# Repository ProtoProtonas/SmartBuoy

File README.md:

# SmartBuoy
Repository for a smart buoy which can navigate to a destination on water and then come back.

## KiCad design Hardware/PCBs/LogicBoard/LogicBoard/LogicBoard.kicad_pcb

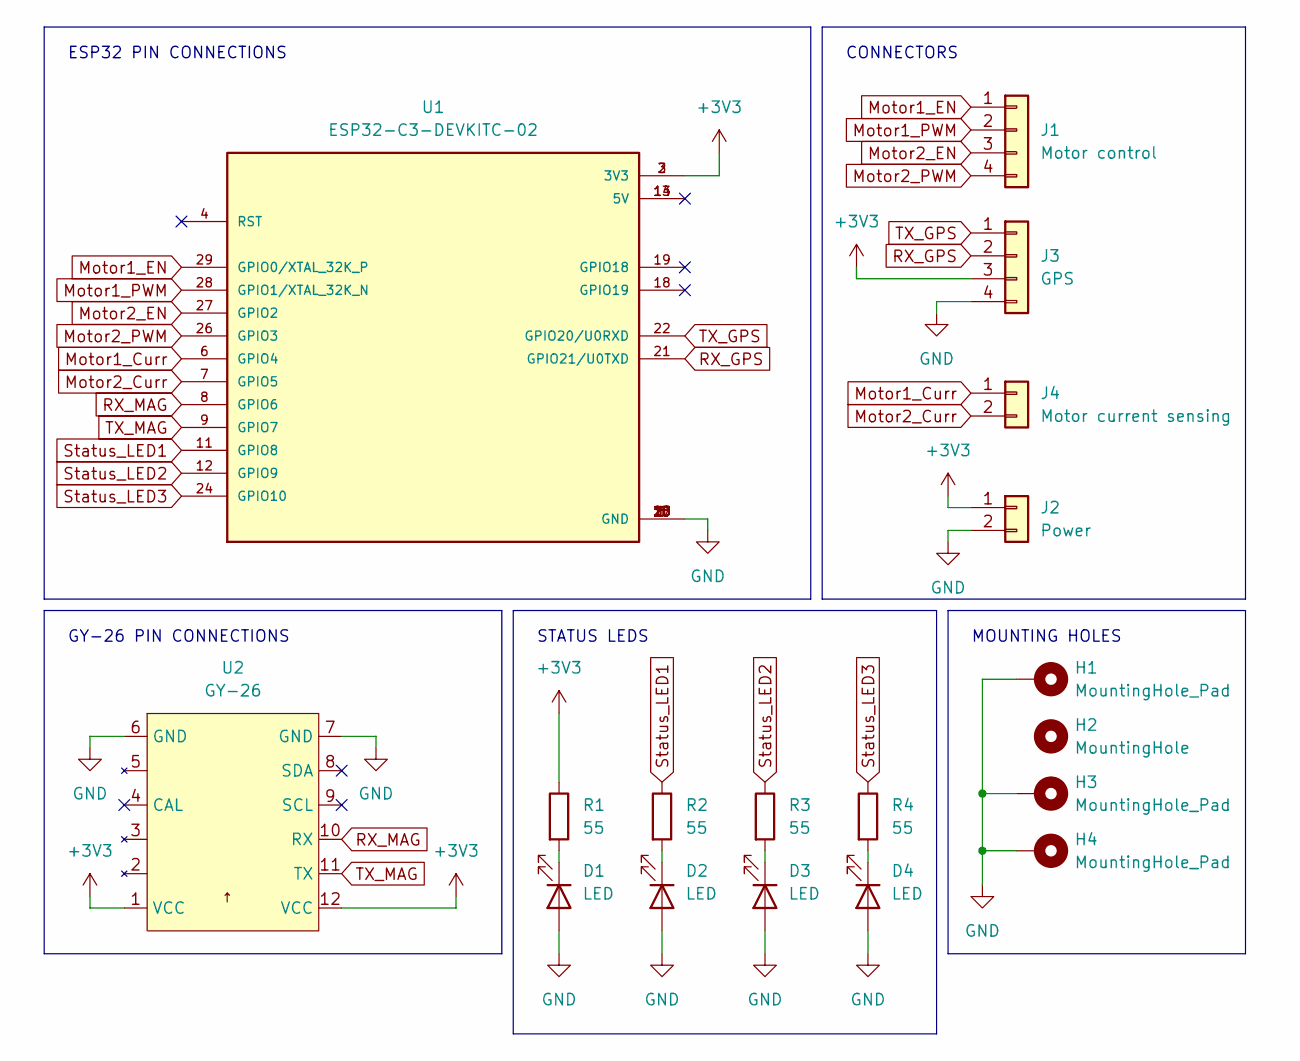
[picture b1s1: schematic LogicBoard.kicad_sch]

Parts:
D1, D2, D3, D4: LED; LED_0603_1608Metric_Pad1.05x0.95mm_HandSolder
H1: MountingHole_Pad; MountingHole_2.2mm_M2_DIN965_Pad_TopBottom
H2: MountingHole; MountingHole_2.2mm_M2_DIN965
H3, H4: MountingHole_Pad; MountingHole_2.2mm_M2_ISO7380_Pad_TopBottom
J1: Motor control; PinHeader_1x04_P2.54mm_Vertical
J2: Power; PinHeader_1x02_P2.54mm_Vertical
J3: GPS; PinHeader_1x04_P2.54mm_Vertical
J4: Motor current sensing; PinHeader_1x02_P2.54mm_Vertical
R1, R2, R3, R4: 55; R_0603_1608Metric_Pad0.98x0.95mm_HandSolder
U1: ESP32-C3-DEVKITC-02; XCVR_ESP32-C3-DEVKITC-02
U2: GY-26

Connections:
+3V3: J2.1, J3.3, R1.1, U1.2 (3V3), U1.3 (3V3), U2.1 (VCC), U2.12 (VCC)
GND: D1.2 (A), D2.2 (A), D3.2 (A), D4.2 (A), H1.1, H3.1, H4.1, J2.2, J3.4, U1.1 (GND), U1.5 (GND), U1.10 (GND), U1.15 (GND), U1.16 (GND), U1.17 (GND), U1.20 (GND), U1.23 (GND), U1.25 (GND), U1.30 (GND), U2.6 (GND), U2.7 (GND)
Motor1_Curr: J4.1, U1.6 (GPIO4)
Motor1_EN: J1.1, U1.29 (GPIO0/XTAL_32K_P)
Motor1_PWM: J1.2, U1.28 (GPIO1/XTAL_32K_N)
Motor2_Curr: J4.2, U1.7 (GPIO5)
Motor2_EN: J1.3, U1.27 (GPIO2)
Motor2_PWM: J1.4, U1.26 (GPIO3)
unnamed: D1.1 (K), R1.2
unnamed: D2.1 (K), R2.2
unnamed: D3.1 (K), R3.2
unnamed: D4.1 (K), R4.2
RX_GPS: J3.2, U1.21 (GPIO21/U0TXD)
RX_MAG: U1.8 (GPIO6), U2.10 (RX)
Status_LED1: R2.1, U1.11 (GPIO8)
Status_LED2: R3.1, U1.12 (GPIO9)
Status_LED3: R4.1, U1.24 (GPIO10)
TX_GPS: J3.1, U1.22 (GPIO20/U0RXD)
TX_MAG: U1.9 (GPIO7), U2.11 (TX)

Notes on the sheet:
MOUNTING HOLES
CONNECTORS
GY-26 PIN CONNECTIONS
STATUS LEDS
ESP32 PIN CONNECTIONS

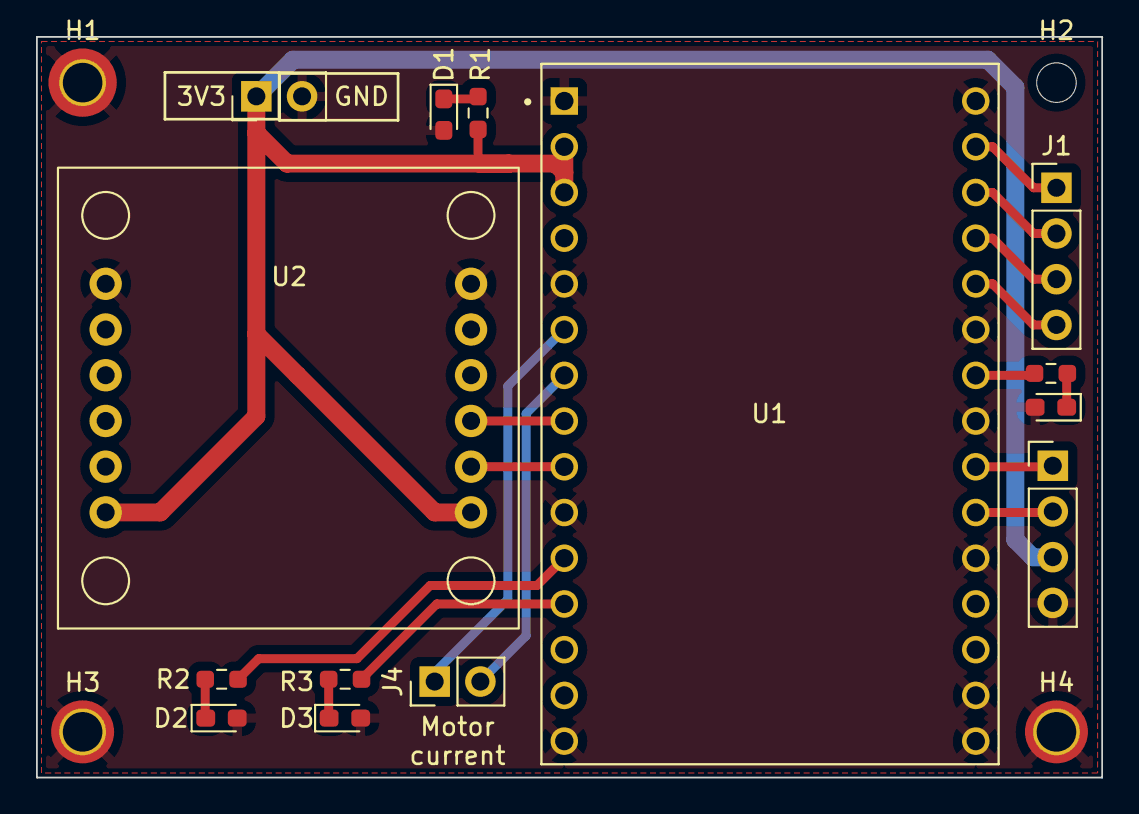
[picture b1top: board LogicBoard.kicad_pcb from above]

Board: 2 copper layers, 59.2 x 41.1 mm, 18 parts (0 on the bottom side), 19 nets.

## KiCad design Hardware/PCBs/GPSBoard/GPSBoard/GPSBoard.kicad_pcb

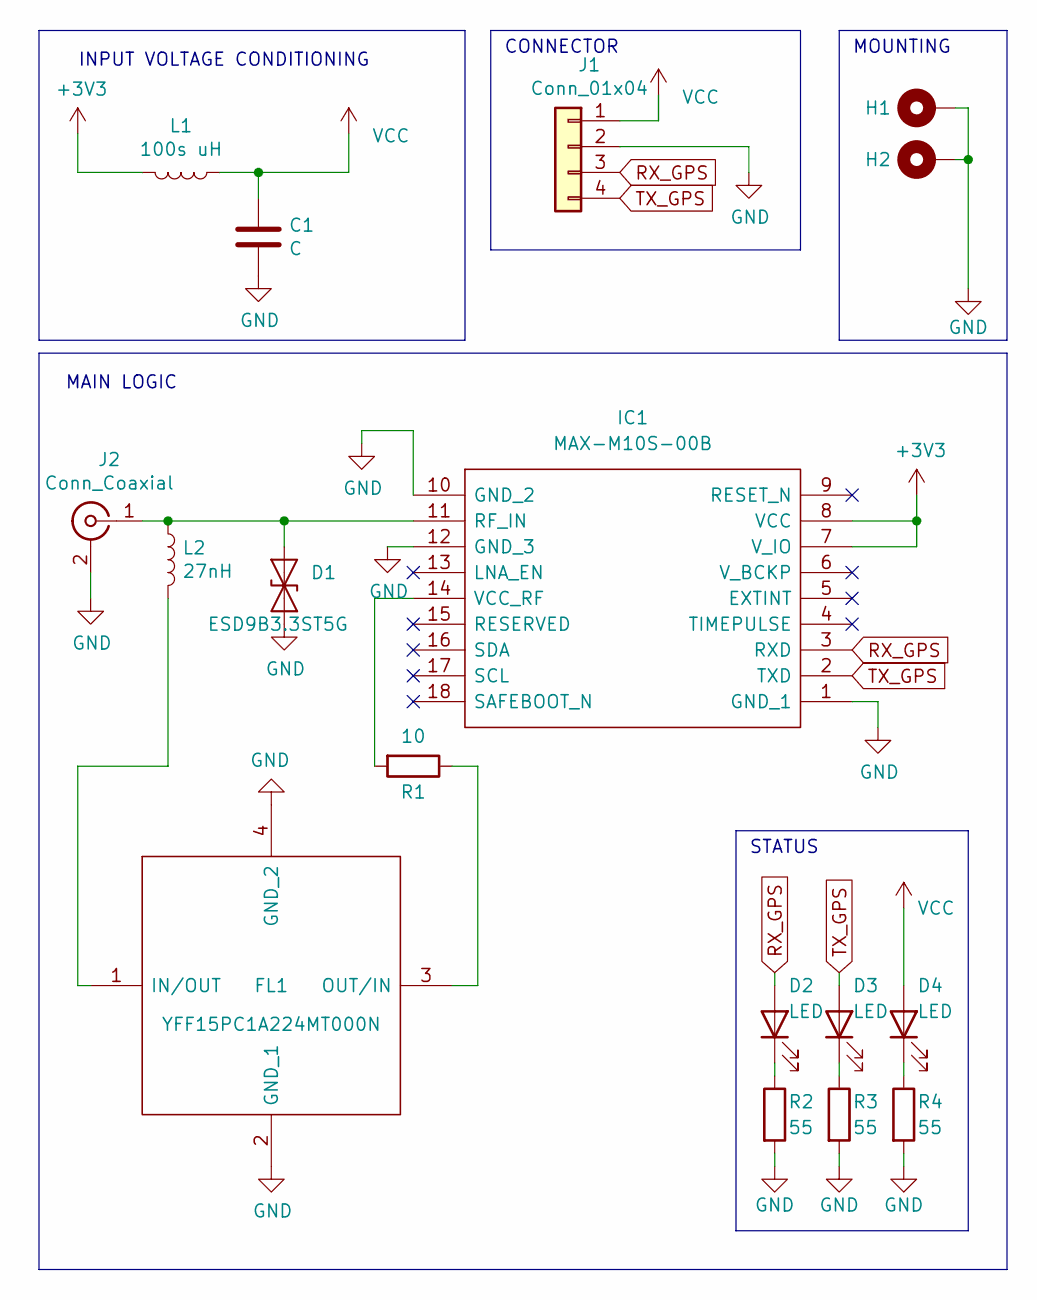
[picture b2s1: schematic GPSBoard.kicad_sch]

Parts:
C1: C; C_1206_3216Metric_Pad1.33x1.80mm_HandSolder
D1: ESD9B3.3ST5G; D_SOD-923
D2, D3, D4: LED; LED_0603_1608Metric_Pad1.05x0.95mm_HandSolder
FL1: YFF15PC1A224MT000N; YFF15PC; Mouser Part Number 810-YFF15PC1A224M
H1, H2: MountingHole_Pad; MountingHole_2.2mm_M2_Pad_TopBottom
IC1: MAX-M10S-00B; MAXM10S00B; Mouser Part Number 377-MAX-M10S-00B
J1: Conn_01x04; PinHeader_1x04_P2.54mm_Vertical
J2: Conn_Coaxial; U.FL_Molex_MCRF_73412-0110_Vertical
L1: 100s uH; L_1206_3216Metric_Pad1.22x1.90mm_HandSolder
L2: 27nH; L_1206_3216Metric_Pad1.22x1.90mm_HandSolder
R1: 10; R_1206_3216Metric_Pad1.30x1.75mm_HandSolder
R2, R3, R4: 55; R_0603_1608Metric_Pad0.98x0.95mm_HandSolder

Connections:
+3V3: IC1.7 (V_IO), IC1.8 (VCC), L1.2
GND: C1.2, D1.1 (A1), FL1.2 (GND_1), FL1.4 (GND_2), H1.1, H2.1, IC1.1 (GND_1), IC1.10 (GND_2), IC1.12 (GND_3), J1.2, J2.2 (Ext), R2.2, R3.2, R4.2
unnamed: D1.2 (A2), IC1.11 (RF_IN), J2.1 (In), L2.1
unnamed: D2.1 (K), R2.1
unnamed: D3.1 (K), R3.1
unnamed: D4.1 (K), R4.1
unnamed: FL1.1 (IN/OUT), L2.2
unnamed: FL1.3 (OUT/IN), R1.1
unnamed: IC1.14 (VCC_RF), R1.2
RX_GPS: D2.2 (A), IC1.3 (RXD), J1.3
TX_GPS: D3.2 (A), IC1.2 (TXD), J1.4
VCC: C1.1, D4.2 (A), J1.1, L1.1

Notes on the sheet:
CONNECTOR
STATUS
MOUNTING
INPUT VOLTAGE CONDITIONING
MAIN LOGIC

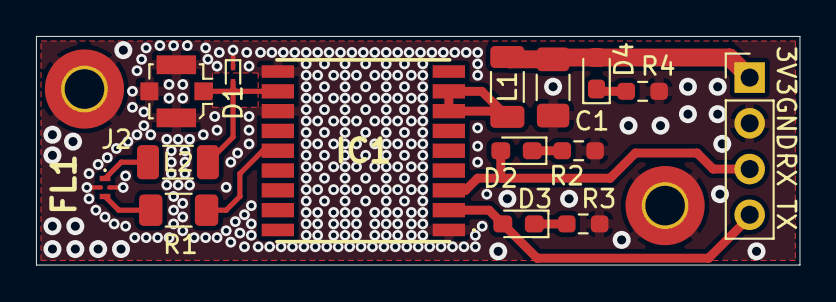
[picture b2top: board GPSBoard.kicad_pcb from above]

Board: 2 copper layers, 42.4 x 12.7 mm, 17 parts (0 on the bottom side), 12 nets.

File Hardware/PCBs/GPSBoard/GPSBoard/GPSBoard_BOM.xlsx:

Source: | C:\Users\Augustas\Desktop\shrot\projektukai\ESP32buoy\git\SmartBuoy\Hardware\PC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
Date: | 44914.83315972222
Tool: | Eeschema (6.0.9)
Generator: | C:\Program Files\KiCad\6.0\bin\scripting\plugins/bom_csv_grouped_by_value_with_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
Component Count: | 19
Ref | Qnty | Value | Cmp name | Footprint | Description | Vendor
C1 , | 1 | 10u | C | Capacitor_SMD:C_1206_3216Metric_Pad1.33x1.80mm_HandSolder | Unpolarized capacitor | https://eu.mouser.com/ProductDetail/KYOCERA-AVX/1206DD106MAT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
C2 , | 1 | <12pF | C_Feedthrough | YFF18AC0G475MT0Y0E:YFF18AC | Feedthrough capacitor | https://eu.mouser.com/ProductDetail/TDK/YFF18AC0G475MT0Y0E?q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
D1 , | 1 | ESD9B3.3ST5G | ESD9B3.3ST5G | Diode_SMD:D_SOD-923 | ESD protection diode, 3.3Vrwm, SOD-923 | https://eu.mouser.com/ProductDetail/onsemi/ESD9B3.3ST5G?qs=y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
D2 ,D3 ,D4 , | 3 | LED | LED | LED_SMD:LED_0603_1608Metric_Pad1.05x0.95mm_HandSolder | Light emitting diode | https://eu.mouser.com/ProductDetail/ROHM-Semiconductor/SML-D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 | https://eu.mouser.com/ProductDetail/Bivar/SM0603UBWC?qs=hWDd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 | https://eu.mouser.com/ProductDetail/Lumex/SML-LX0603GW-TR?qs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 | https://eu.mouser.com/ProductDetail/Lumex/SML-LXIL0603SYC-TR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
H1 ,H2 ,H3 ,H4 , | 4 | MountingHole_Pad | MountingHole_Pad | MountingHole:MountingHole_2.2mm_M2_Pad_TopBottom | Mounting Hole with connection
IC1 , | 1 | MAX-M10S-00B | MAX-M10S-00B | UBLOX_GPS:MAXM10S00B | GPS Modules u-blox M10 GNSS LCC module, firmware in ROM, SAW filter, LNA | https://eu.mouser.com/ProductDetail/u-blox/MAX-M10S-00B?qs=A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
J1 , | 1 | Conn_01x04 | Conn_01x04 | Connector_PinHeader_2.54mm:PinHeader_1x04_P2.54mm_Vertical | Generic connector, single row, 01x04, script generated (kicad-library-utils/sch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 | https://eu.mouser.com/ProductDetail/Wurth-Elektronik/6130401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
J2 , | 1 | Conn_Coaxial | Conn_Coaxial | Connector_Coaxial:U.FL_Hirose_U.FL-R-SMT-1_Vertical | coaxial connector (BNC, SMA, SMB, SMC, Cinch/RCA, LEMO, ...) | https://eu.mouser.com/ProductDetail/Linx-Technologies/CONUFL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
L1 , | 1 | 100s uH | L | Inductor_SMD:L_1206_3216Metric_Pad1.22x1.90mm_HandSolder | Inductor | https://eu.mouser.com/ProductDetail/Murata-Electronics/LQM31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
L2 , | 1 | 27nH | L | Inductor_SMD:L_1206_3216Metric_Pad1.22x1.90mm_HandSolder | Inductor | https://eu.mouser.com/ProductDetail/Coilcraft/1206CS-270XGLC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 | https://eu.mouser.com/ProductDetail/Murata-Electronics/LQW31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
R1 , | 1 | 10 | R | Resistor_SMD:R_1206_3216Metric_Pad1.30x1.75mm_HandSolder | Resistor | https://eu.mouser.com/ProductDetail/Bourns/CRT1206-BY-10R0EL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
R2 ,R3 ,R4 , | 3 | 55 | R | Resistor_SMD:R_0603_1608Metric_Pad0.98x0.95mm_HandSolder | Resistor | https://eu.mouser.com/ProductDetail/Vishay-Dale/CRCW060356R0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
 |  |  |  |  |  | https://eu.mouser.com/ProductDetail/Linx-Technologies/ANT-GN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

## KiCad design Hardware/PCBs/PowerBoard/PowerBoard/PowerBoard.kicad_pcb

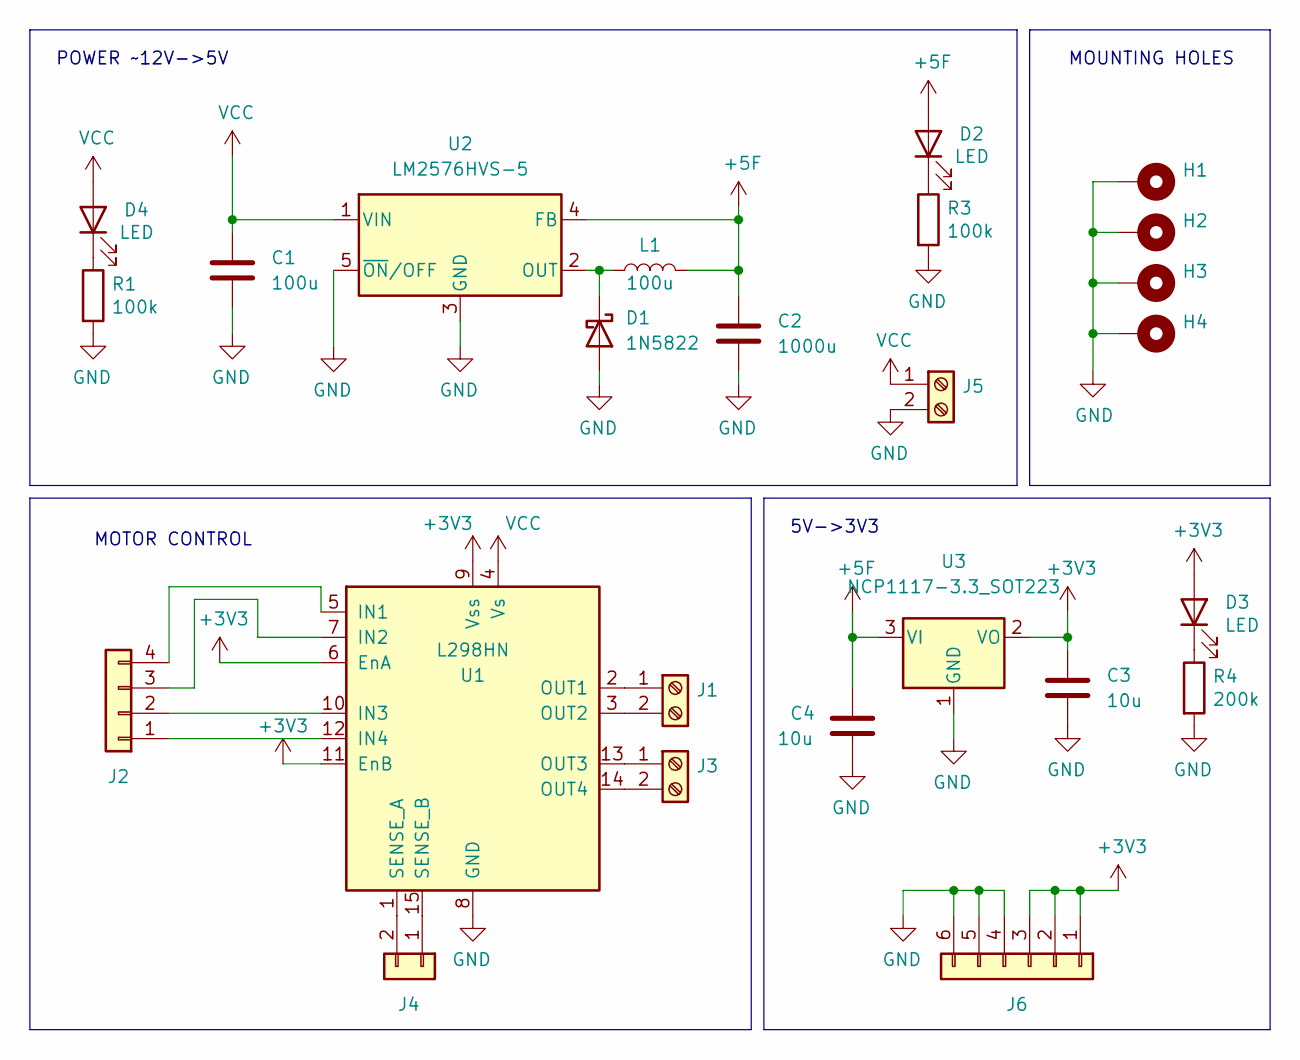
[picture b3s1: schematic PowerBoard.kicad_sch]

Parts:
C1: 100u; CP_Radial_D8.0mm_P3.50mm
C2: 1000u; CP_Radial_D16.0mm_P7.50mm
C3, C4: 10u; C_1206_3216Metric_Pad1.33x1.80mm_HandSolder
D1: 1N5822; D_DO-201AD_P15.24mm_Horizontal
D2, D3, D4: LED; LED_D5.0mm
H1, H2, H3, H4: MountingHole_Pad; MountingHole_3.2mm_M3_DIN965_Pad_TopBottom
J1, J3, J5: Screw_Terminal_01x02; TerminalBlock_bornier-2_P5.08mm
J2: Conn_01x04; PinSocket_1x04_P2.54mm_Vertical
J4: Conn_01x02; PinSocket_1x02_P2.54mm_Vertical
J6: Conn_01x06; PinSocket_1x06_P2.54mm_Vertical
L1: 100u; L_1812_4532Metric_Pad1.30x3.40mm_HandSolder
R1: 100k; R_0603_1608Metric_Pad0.98x0.95mm_HandSolder
R3: 100k; R_0805_2012Metric_Pad1.20x1.40mm_HandSolder
R4: 200k; R_0603_1608Metric_Pad0.98x0.95mm_HandSolder
U1: L298HN; TO-220-15_P2.54x2.54mm_StaggerOdd_Lead4.58mm_Vertical
U2: LM2576HVS-5; TO-263-5_TabPin3
U3: NCP1117-3.3_SOT223; SOT-223-3_TabPin2

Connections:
+3V3: C3.1, D3.2 (A), J6.1, J6.2, J6.3, U1.6 (EnA), U1.9 (Vss), U1.11 (EnB), U3.2 (VO)
+5F: C2.1, C4.1, D2.2 (A), L1.2, U2.4 (FB), U3.3 (VI)
GND: C1.2, C2.2, C3.2, C4.2, D1.2 (A), H1.1, H2.1, H3.1, H4.1, J5.2, J6.4, J6.5, J6.6, R1.2, R3.2, R4.2, U1.8 (GND), U2.3 (GND), U2.5 (~ON/OFF), U3.1 (GND)
unnamed: D1.1 (K), L1.1, U2.2 (OUT)
unnamed: D2.1 (K), R3.1
unnamed: D3.1 (K), R4.1
unnamed: D4.1 (K), R1.1
unnamed: J1.1, U1.2 (OUT1)
unnamed: J1.2, U1.3 (OUT2)
unnamed: J2.1, U1.12 (IN4)
unnamed: J2.2, U1.10 (IN3)
unnamed: J2.3, U1.7 (IN2)
unnamed: J2.4, U1.5 (IN1)
unnamed: J3.1, U1.13 (OUT3)
unnamed: J3.2, U1.14 (OUT4)
unnamed: J4.1, U1.15 (SENSE_B)
unnamed: J4.2, U1.1 (SENSE_A)
VCC: C1.1, D4.2 (A), J5.1, U1.4 (Vs), U2.1 (VIN)

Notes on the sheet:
POWER ~12V->5V
MOTOR CONTROL
MOUNTING HOLES
5V->3V3

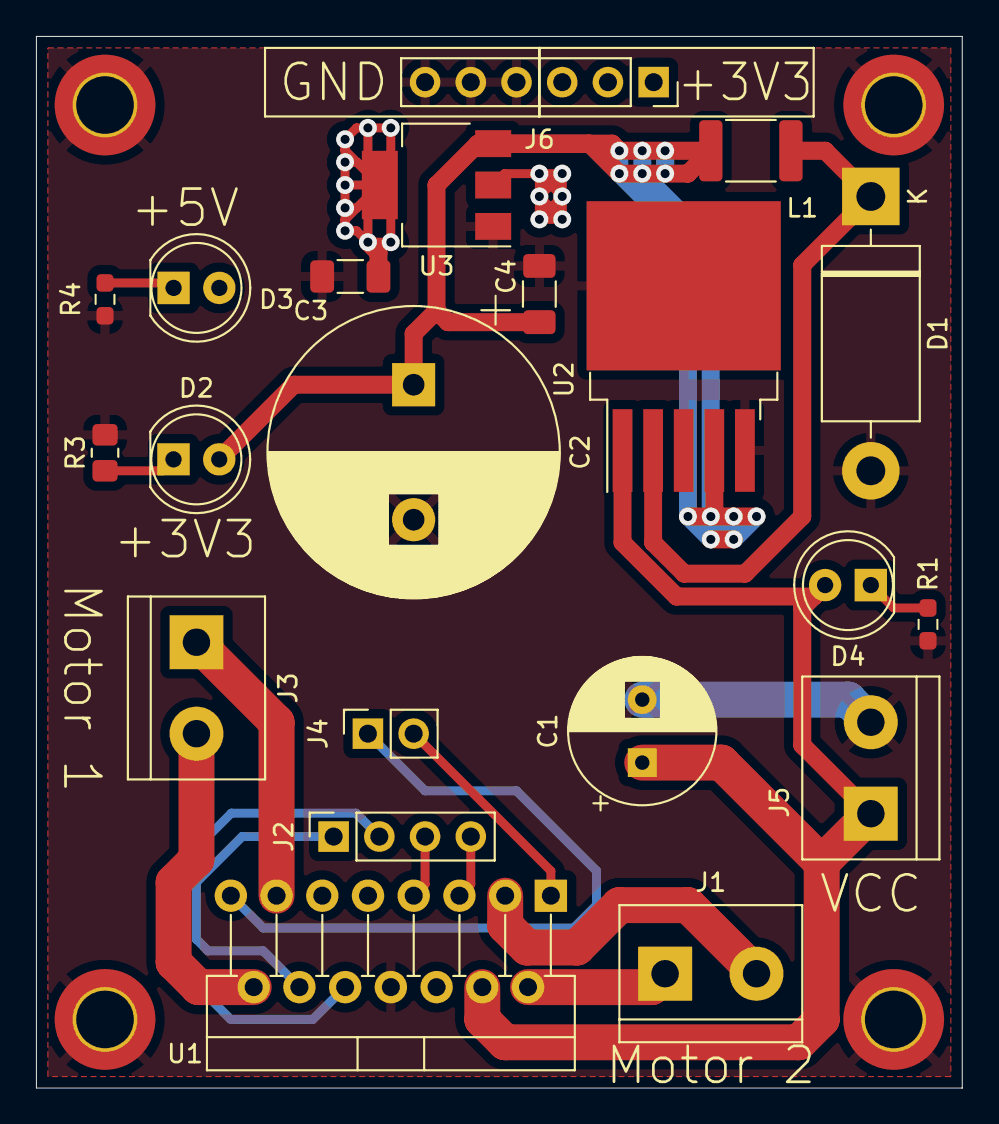
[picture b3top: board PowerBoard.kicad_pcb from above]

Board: 2 copper layers, 51.4 x 58.4 mm, 25 parts (0 on the bottom side), 18 nets.

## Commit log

2022-03-12 Added check if GPS position is valid
2022-03-12 Added motor control wrapper
2022-03-26 Added comments where device needs to be calibrated
2022-04-13 Folder structure added
2022-04-16 Added global class to handle common methods and data
2022-04-16 Added variables to the global class
2022-04-16 Formatting
2022-04-16 Target destination switching based on time elapsed
2022-04-17 PinDefines.h added
2022-04-17 Averager template added for GPS and compass sensors
2022-04-17 Update TODO.txt file
2022-04-17 Remove unused moving average class
2022-04-17 PCB + more folders added
2022-04-19 Finished power schematic and L298 wiring
2022-04-20 PCB component footprints added
2022-04-22 PCB routed
2022-05-17 Added ground planes and mounting holes
2022-06-25 Added third mounting hole
2022-07-05 Created projects for logic and GPS boards, started working on GPS
2022-07-06 GPS board schematic created
2022-07-10 GPS PCB designed
2022-11-22 Rewamped power board
2022-11-22 Removed backup archives
2022-12-25 Designed GPS board
2023-01-01 Added silkscreen
2023-01-01 Added BOM
